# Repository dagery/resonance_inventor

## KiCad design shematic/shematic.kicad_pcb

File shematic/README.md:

# LLC resonance inventor

LLC resonance inventor To Do List:
Do All!

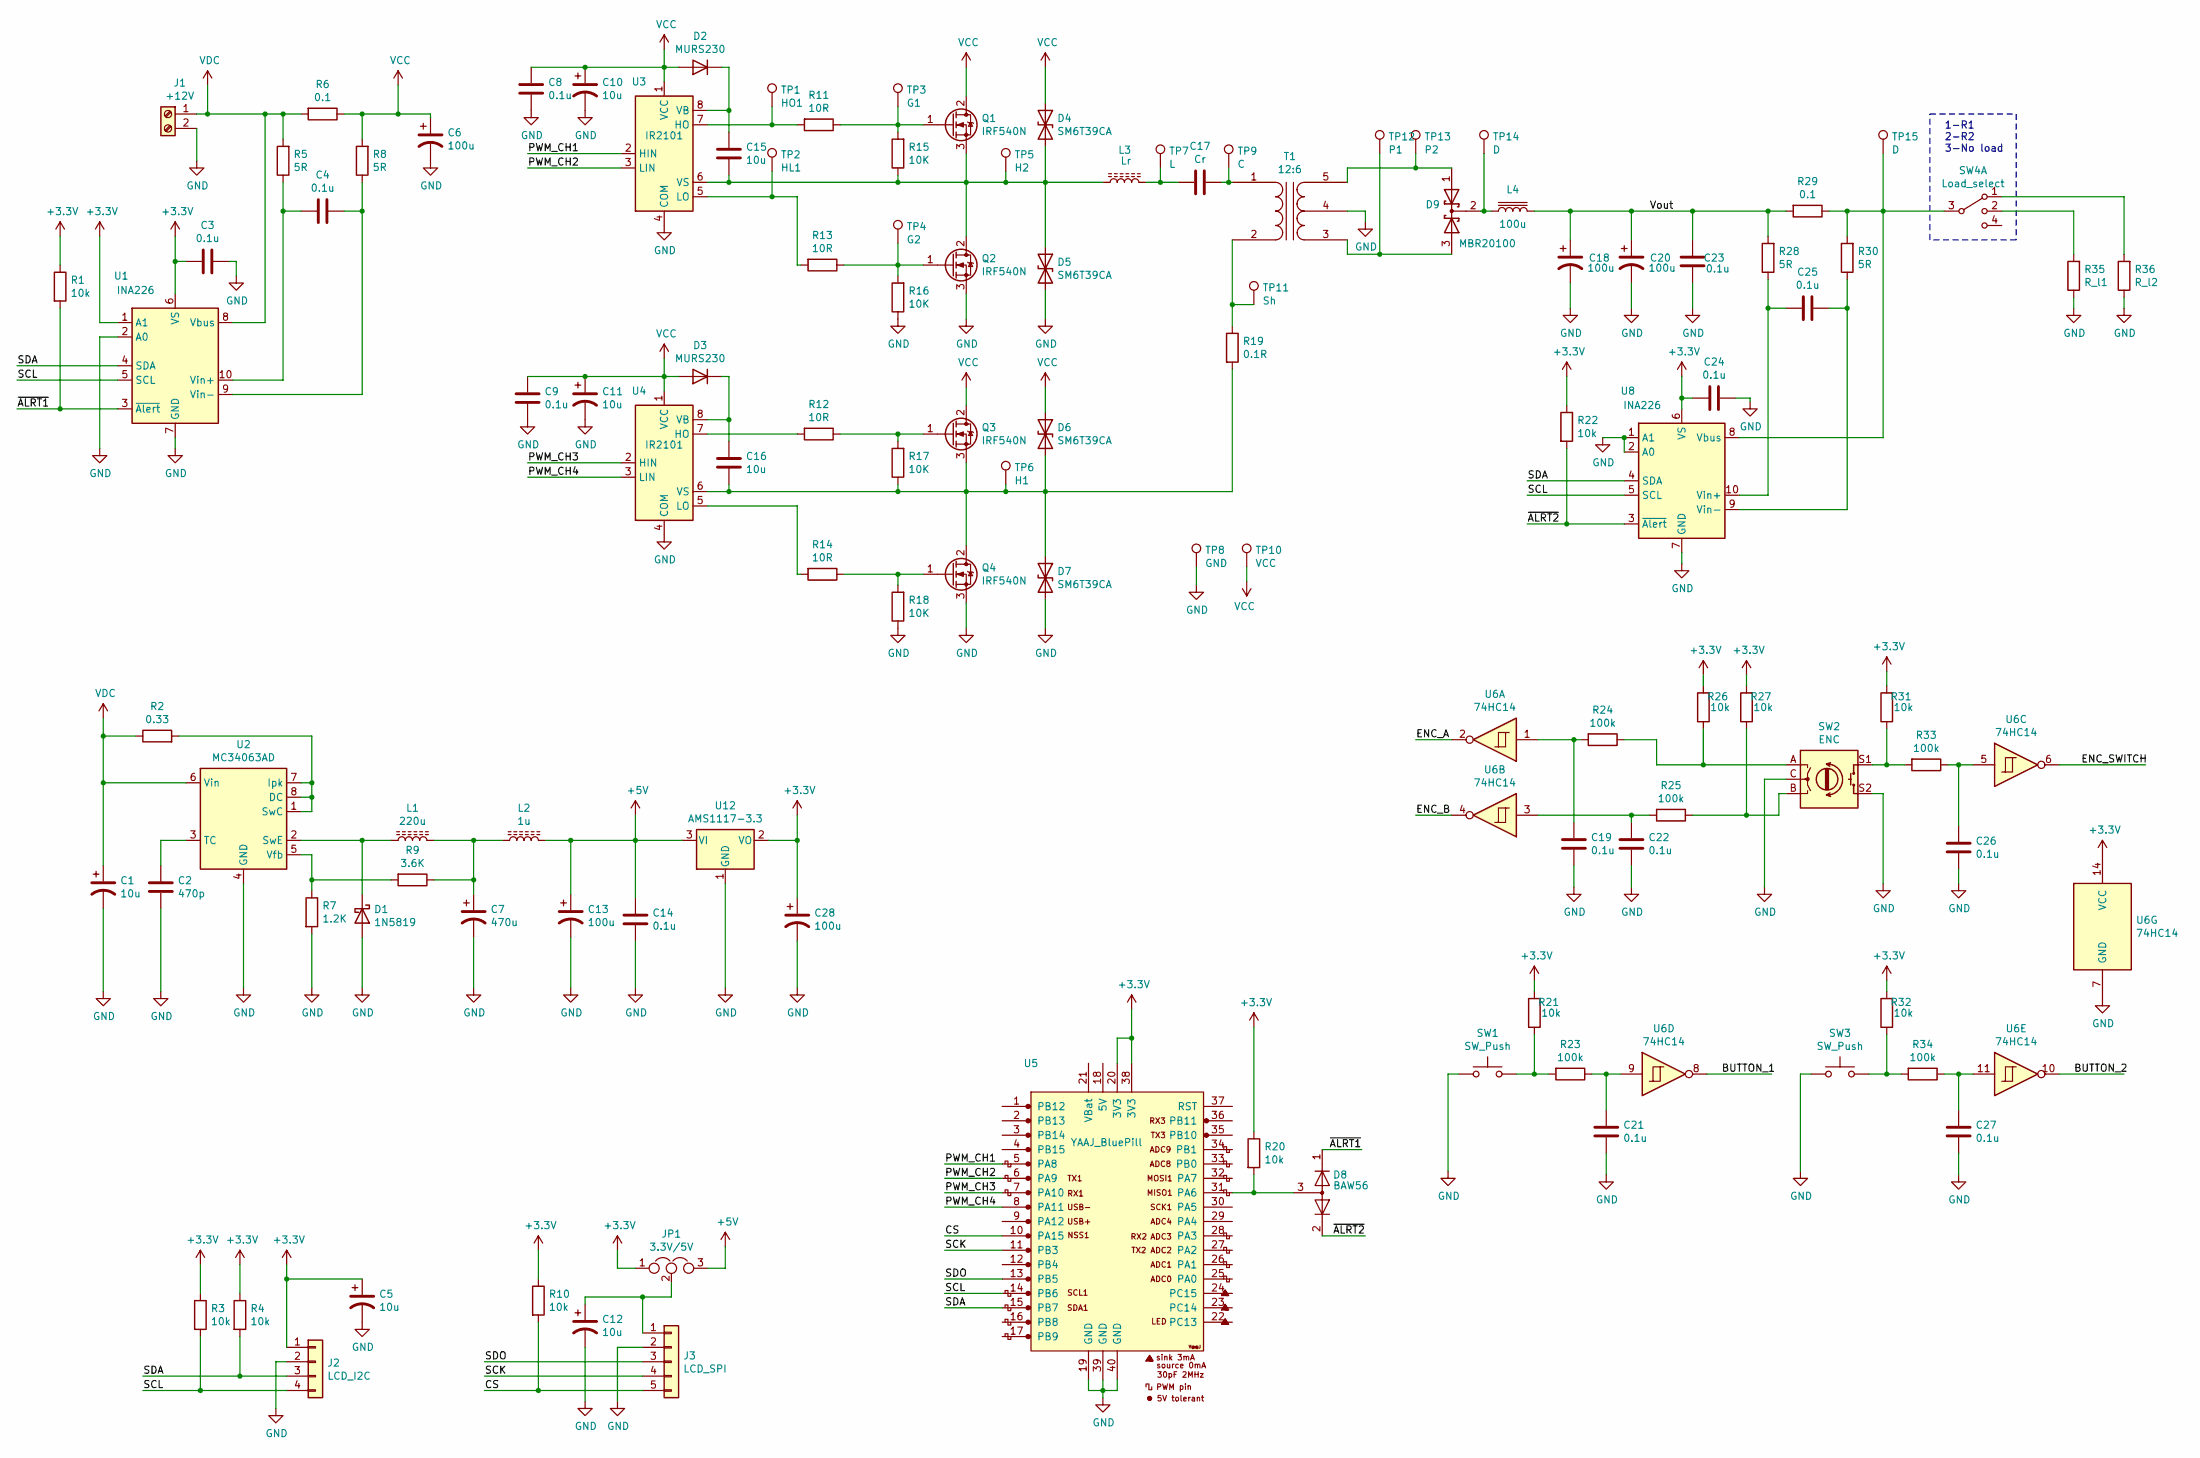
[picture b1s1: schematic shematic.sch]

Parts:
C1: 10u; CP_EIA-3528-21_Kemet-B
C2: 470p; C_1206_3216Metric
C3, C8, C9, C14, C19, C21, C22, C23, C24, C26, C27: 0.1u; C_1206_3216Metric
C4, C25: 0.1u; C_0805_2012Metric
C5, C10, C11, C12, C15, C16: 10u; C_1206_3216Metric
C6, C18, C20, C28: 100u; CP_Radial_D8.0mm_P3.50mm
C7: 470u; CP_Radial_D8.0mm_P3.50mm
C13: 100u; CP_EIA-7343-31_Kemet-D
C17: Cr; C_Rect_L11.5mm_W5.0mm_P10.00mm_MKT
D1: 1N5819; D_SOD-123
D2, D3: MURS230; D_SMB
D4, D5, D6, D7: SM6T39CA; D_SMB
D8: BAW56; SOT-23
D9: MBR20100; TO-220-3_Vertical
J1: +12V; TerminalBlock_bornier-2_P5.08mm
J2: LCD_I2C; PinHeader_1x04_P2.54mm_Vertical
J3: LCD_SPI; PinHeader_1x05_P2.54mm_Vertical
JP1: 3.3V/5V; SolderJumper-3_P1.3mm_Open_Pad1.0x1.5mm
L1: 220u; L_Bourns_SRN6045TA
L2: 1u; L_Bourns_SRN6045TA
L3: Lr; L_Radial_D10.5mm_P4.00x5.00mm_Murata_1200RS
L4: 100u; L_Toroid_Vertical_L24.6mm_W15.5mm_P11.44mm_Pulse_KM-4
Q1, Q2, Q3, Q4: IRF540N; TO-220-3_Vertical
R1, R3, R4, R10, R20, R21, R22, R26, R27, R31, R32: 10k; R_1206_3216Metric
R2: 0.33; R_1206_3216Metric
R5, R8, R28, R30: 5R; R_0805_2012Metric
R6, R29: 0.1; R_2512_6332Metric
R7: 1.2K; R_1206_3216Metric
R9: 3.6K; R_1206_3216Metric
R11, R12, R13, R14: 10R; R_1206_3216Metric
R15, R16, R17, R18: 10K; R_1206_3216Metric
R19: 0.1R; R_2512_6332Metric
R23, R24, R25, R33, R34: 100k; R_1206_3216Metric
R35: R_l1; R_Axial_Power_L25.0mm_W6.4mm_P30.48mm
R36: R_l2; R_Axial_Power_L25.0mm_W6.4mm_P30.48mm
SW1, SW3: SW_Push; SW_PUSH_6mm_H8.5mm
SW2: ENC; RotaryEncoder_Alps_EC11E-Switch_Vertical_H20mm_CircularMoun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
SW4: Load_select; PinHeader_1x04_P2.54mm_Vertical
T1: 12:6; Transformer_EPCOS_B66359A1013T_Horizontal_My
TP1: HO1; Pin_D1.0mm_L10.0mm
TP2: HL1; Pin_D1.0mm_L10.0mm
TP3: G1; Pin_D1.0mm_L10.0mm
TP4: G2; Pin_D1.0mm_L10.0mm
TP5: H2; Pin_D1.0mm_L10.0mm
TP6: H1; Pin_D1.0mm_L10.0mm
TP7: L; Pin_D1.0mm_L10.0mm
TP8: GND; Pin_D1.0mm_L10.0mm
TP9: C; Pin_D1.0mm_L10.0mm
TP10: VCC; Pin_D1.0mm_L10.0mm
TP11: Sh; Pin_D1.0mm_L10.0mm
TP12: P1; Pin_D1.0mm_L10.0mm
TP13: P2; Pin_D1.0mm_L10.0mm
TP14, TP15: D; Pin_D1.0mm_L10.0mm
U1, U8: INA226; VSSOP-10_3x3mm_P0.5mm
U2: MC34063AD; SOIC-8_3.9x4.9mm_P1.27mm
U3, U4: IR2101; DIP-8_W7.62mm_LongPads
U5: YAAJ_BluePill; YAAJ_BluePill_1
U6: 74HC14; SO-14_3.9x8.65mm_P1.27mm
U12: AMS1117-3.3; SOT-223-3_TabPin2

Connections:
+3V3: C3.2, C5.1, C24.2, C28.1, J2.1, JP1.1, R1.1, R3.1, R4.1, R10.1, R20.1, R21.2, R22.1, R26.2, R27.2, R31.2, R32.2, U1.1 (A1), U1.6 (VS), U5.20 (3V3), U5.38 (3V3), U6.14 (VCC), U8.6 (VS), U12.2 (VO)
+5V: C13.1, C14.2, JP1.3, L2.2, U12.3 (VI)
/BUTTON_1: U6.8
/BUTTON_2: U6.10
/CS: J3.5, R10.2, U5.10 (PA15)
/ENC_A: U6.2
/ENC_B: U6.4
/ENC_SWITCH: U6.6
/PWM_CH1: U3.2 (HIN), U5.5 (PA8)
/PWM_CH2: U3.3 (LIN), U5.6 (PA9)
/PWM_CH3: U4.2 (HIN), U5.7 (PA10)
/PWM_CH4: U4.3 (LIN), U5.8 (PA11)
/SCK: J3.4, U5.11 (PB3)
/SCL: J2.4, R3.2, U1.5 (SCL), U5.14 (PB6), U8.5 (SCL)
/SDA: J2.3, R4.2, U1.4 (SDA), U5.15 (PB7), U8.4 (SDA)
/SDO: J3.3, U5.13 (PB5)
/Vout: C18.1, C20.1, C23.2, L4.2, R28.2, R29.2
/~ALRT1: D8.1 (K), R1.2, U1.3 (~Alert~)
/~ALRT2: D8.2 (A), R22.2, U8.3 (~Alert~)
GND: C1.2, C2.1, C3.1, C5.2, C6.2, C7.2, C8.1, C9.1, C10.2, C11.2, C12.2, C13.2, C14.1, C18.2, C19.2, C20.2, C21.2, C22.2, C23.1, C24.1, C26.2, C27.2, C28.2, D1.2 (A), D5.2 (A2), D7.2 (A2), J1.2, J2.2, J3.2, Q2.3 (S), Q4.3 (S), R7.2, R16.1, R18.1, R35.1, R36.1, SW1.1, SW2.C, SW2.S2, SW3.1, T1.4 (SC), TP8.1, U1.2 (A0), U1.7 (GND), U2.4 (GND), U3.4 (COM), U4.4 (COM), U5.19 (GND), U5.39 (GND), U5.40 (GND), U6.7 (GND), U8.1 (A1), U8.2 (A0), U8.7 (GND), U12.1 (GND)
unnamed: C2.2, U2.3 (TC)
unnamed: C4.1, R8.1, U1.9 (Vin-)
unnamed: C4.2, R5.1, U1.10 (Vin+)
unnamed: C7.1, L1.2, L2.1, R9.1
unnamed: C12.1, J3.1, JP1.2
unnamed: C15.1, D4.2 (A2), D5.1 (A1), L3.1, Q1.3 (S), Q2.2 (D), R15.1, TP5.1, U3.6 (VS)
unnamed: C15.2, D2.2 (K), U3.8 (VB)
unnamed: C16.1, D6.2 (A2), D7.1 (A1), Q3.3 (S), Q4.2 (D), R17.1, R19.2, TP6.1, U4.6 (VS)
unnamed: C16.2, D3.2 (K), U4.8 (VB)
unnamed: C17.1, T1.1 (AA), TP9.1
unnamed: C17.2, L3.2, TP7.1
unnamed: C19.1, R24.2, U6.1
unnamed: C21.1, R23.1, U6.9
unnamed: C22.1, R25.2, U6.3
unnamed: C25.1, R30.1, U8.9 (Vin-)
unnamed: C25.2, R28.1, U8.10 (Vin+)
unnamed: C26.1, R33.1, U6.5
unnamed: C27.1, R34.1, U6.11
unnamed: D1.1 (K), L1.1, U2.2 (SwE)
unnamed: D8.3 (K), R20.2, U5.31 (PA6)
unnamed: D9.1 (A), T1.5 (SB), TP13.1
unnamed: D9.2 (K), L4.1, TP14.1
unnamed: D9.3 (A), T1.3 (SA), TP12.1
unnamed: Q1.1 (G), R11.1, R15.2, TP3.1
unnamed: Q2.1 (G), R13.1, R16.2, TP4.1
unnamed: Q3.1 (G), R12.1, R17.2
unnamed: Q4.1 (G), R14.1, R18.2
unnamed: R2.2, U2.1 (SwC), U2.7 (Ipk), U2.8 (DC)
unnamed: R7.1, R9.2, U2.5 (Vfb)
unnamed: R11.2, TP1.1, U3.7 (HO)
unnamed: R12.2, U4.7 (HO)
unnamed: R13.2, TP2.1, U3.5 (LO)
unnamed: R14.2, U4.5 (LO)
unnamed: R19.1, T1.2 (AB), TP11.1
unnamed: R21.1, R23.2, SW1.2
unnamed: R24.1, R26.1, SW2.A
unnamed: R25.1, R27.1, SW2.B
unnamed: R29.1, R30.2, SW4.3, TP15.1, U8.8 (Vbus)
unnamed: R31.1, R33.2, SW2.S1
unnamed: R32.1, R34.2, SW3.2
unnamed: R35.2, SW4.2
unnamed: R36.2, SW4.1
VCC: C6.1, C8.2, C9.2, C10.1, C11.1, D2.1 (A), D3.1 (A), D4.1 (A1), D6.1 (A1), Q1.2 (D), Q3.2 (D), R6.1, R8.2, TP10.1, U3.1 (VCC), U4.1 (VCC)
VDC: C1.1, J1.1, R2.1, R5.2, R6.2, U1.8 (Vbus), U2.6 (Vin)

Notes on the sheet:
1-R1 2-R2 3-No load

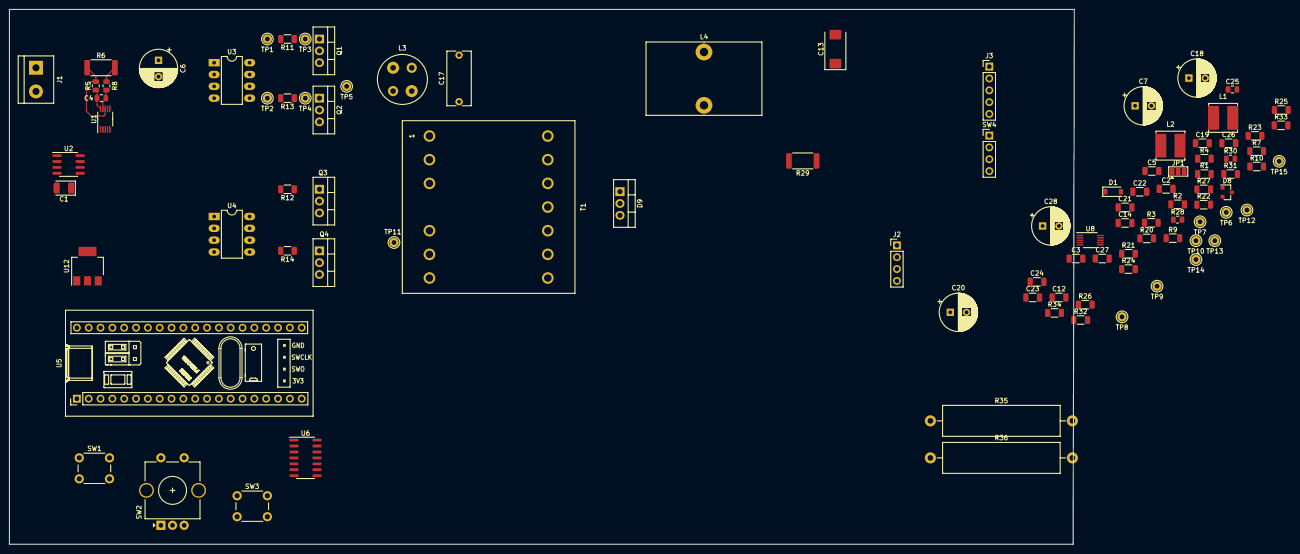
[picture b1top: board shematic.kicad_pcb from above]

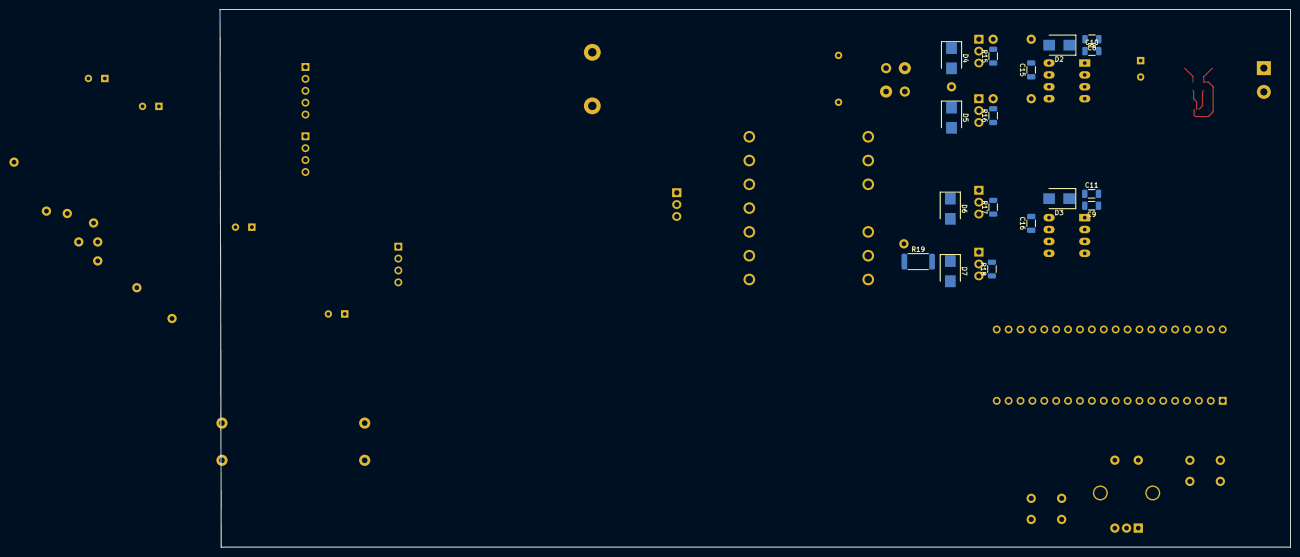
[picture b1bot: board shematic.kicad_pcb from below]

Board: 2 copper layers, 228.6 x 114.8 mm, 113 parts (17 on the bottom side), 59 nets.

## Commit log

2021-12-09 Added code folder with STM32IDE project
